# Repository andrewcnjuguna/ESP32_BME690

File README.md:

# ESP32_BME690

Multi-room ESP32-S3 environmental sensor node that streams air-quality data
to a Node.js server over Wi-Fi. Built around the Bosch BME690 with auxiliary
light, sound and battery monitoring.

## Hardware

- ESP32-S3-WROOM-1 module
- Bosch **BME690** (I2C) — temperature, humidity, pressure, IAQ, CO2eq, bVOC
- SH1106 0.96" OLED (I2C)
- TEMT6000 ambient light sensor
- Analog MEMS microphone (sound level)
- 1-cell LiPo with 1M/1M voltage divider on the battery rail
- USB-C power / programming
- Status LED

KiCad project lives in [hardware/kicad/](hardware/kicad/).

### Pin map

| Function    | GPIO |
|-------------|------|
| I2C SDA     | 8    |
| I2C SCL     | 9    |
| Status LED  | 2    |
| Light sensor (TEMT6000) | 5 |
| Microphone  | 4    |
| VBAT sense  | 1    |

## Firmware

Sketches live in [firmware/](firmware/).

- `ESP32_BME690_usb/` — main node firmware
- `battery_level/`, `light_sensor_test/`, `sound_sensor/` — bring-up sketches

### Setup

1. Open `firmware/ESP32_BME690_usb/` in the Arduino IDE.
2. Copy `secrets.h.example` → `secrets.h` and fill in your Wi-Fi credentials
   and server URL. `secrets.h` is gitignored.
3. Install required libraries: `Adafruit GFX`, `Adafruit SH110X`,
   `BSEC2` (Bosch), `ArduinoJson`, `ArduinoOTA`.
4. Build & flash. The `locationID` constant in the sketch tags this node's
   data on the server (e.g. `Kitchen`, `Living_Room`).

### Node web page (port 80)

Each node runs its own tiny status page at `http://<node-ip>/`
(auto-refreshes every 5 s). It shows the live BSEC readings, light / sound /
battery, **WiFi signal** (RSSI in dBm, an approximate 0–100 % quality, and a
label Excellent/Good/Fair/Weak/Poor), and the SD-log status. If the SD card
is mounted it also links `http://<node-ip>/datalog.csv` to download the full
log.

The node's IP is printed on the serial console at boot
(`[INFO] Web UI at http://...`).

WiFi is self-healing: if the router is down at boot (or the link drops
later), the node keeps logging to SD and retries the connection every 30 s
in the background; OTA and the web page start automatically as soon as the
first connection succeeds — no reboot needed.

### Data upload

Every 3 s BSEC cycle the node POSTs a JSON snapshot to `SERVER_URL`
(`/sensor-data` on the dashboard server). The payload includes `location`,
all sensor channels, and the WiFi link quality (`rssi` in dBm plus a derived
`wifiPercent`). Nodes running older firmware simply omit the WiFi fields —
the dashboard shows "not reported (update firmware)" for them.

## Server (dashboard)

A small Node/Express app in [server/](server/) collects POSTs from each node
and serves a per-room dashboard.

```bash
cd server
npm install express
node server.js
```

Then point a browser at `http://<host>:3000`.

- `POST /sensor-data` — nodes push their JSON snapshot here.
- `GET /data` — latest snapshot of every room, as JSON.
- `GET /` — dashboard. Room boxes are created dynamically from whatever
  `location` tags have reported, so adding a node needs **no server change**.
  Each box shows the air-quality channels plus battery and WiFi signal
  quality for that node.

The `pi_server` notes file documents the systemd / iptables setup used on
the home Raspberry Pi.

## Data logging & plotting

### SD card log

The node averages its 3 s BSEC samples and appends **one CSV row per minute**
to `/datalog.csv` on the SD card:

```
boot_id,uptime_s,epoch,synced,temp_c,hum_pct,press_hpa,iaq,iaq_acc,
co2_ppm,voc_ppm,lux,sound_db,sound_avg,sound_peak,batt_v,batt_pct
```

- `boot_id` — power-session counter (persisted in EEPROM), groups rows from
  one uninterrupted run.
- `uptime_s` — seconds since boot (monotonic, rollover-safe).
- `epoch` / `synced` — Unix time and whether NTP had synced when the row was
  written. Rows logged *before* the sync have `epoch=0`, but their true time
  is still recoverable (see below).
- `iaq_acc` — BSEC accuracy 0–3; air-quality values below your chosen
  threshold are warm-up noise.

Grab the file over WiFi from `http://<node-ip>/datalog.csv`, or pull the
card.

### Plotting with `analysis/plot_datalog.py`

```bash
pip install pandas matplotlib
python analysis/plot_datalog.py datalog.csv            # plot a local file
python analysis/plot_datalog.py --ip 192.168.0.65      # fetch straight from the node
python analysis/plot_datalog.py datalog.csv -o out.png # save instead of showing
python analysis/plot_datalog.py datalog.csv --last 48  # last 48 h only
python analysis/plot_datalog.py datalog.csv --min-accuracy 3  # strict AQ filter
```

The script produces six stacked, time-aligned panels: temp+humidity,
pressure, IAQ, CO₂eq+VOCeq, light+sound, and battery. Under the hood it:

1. **Reconstructs absolute time.** For each `boot_id` it derives
   `boot_epoch = epoch − uptime_s` from the NTP-synced rows, then stamps
   *every* row of that session as `boot_epoch + uptime_s` — so even rows
   logged before the NTP sync get correct timestamps. Sessions that never
   synced have no time anchor and are dropped with a warning.
2. **Masks warm-up air-quality data.** IAQ/CO₂/VOC are blanked where
   `iaq_acc < --min-accuracy` (default 1) so BSEC's calibration period
   doesn't draw misleading flat lines.
3. **Breaks lines at gaps.** Rows are minutely, so a jump larger than
   `--gap-min` (default 5 min) means the node was off; a NaN break is
   inserted so downtime shows as a blank gap instead of a false straight
   line across it.

## Repo layout

```
firmware/   Arduino sketches (main + bring-up)
server/     Node/Express dashboard
analysis/   plot_datalog.py — CSV log plotting
hardware/   KiCad project + design notes
images/     PCB photos
```

Component datasheets are kept locally only (not redistributable).

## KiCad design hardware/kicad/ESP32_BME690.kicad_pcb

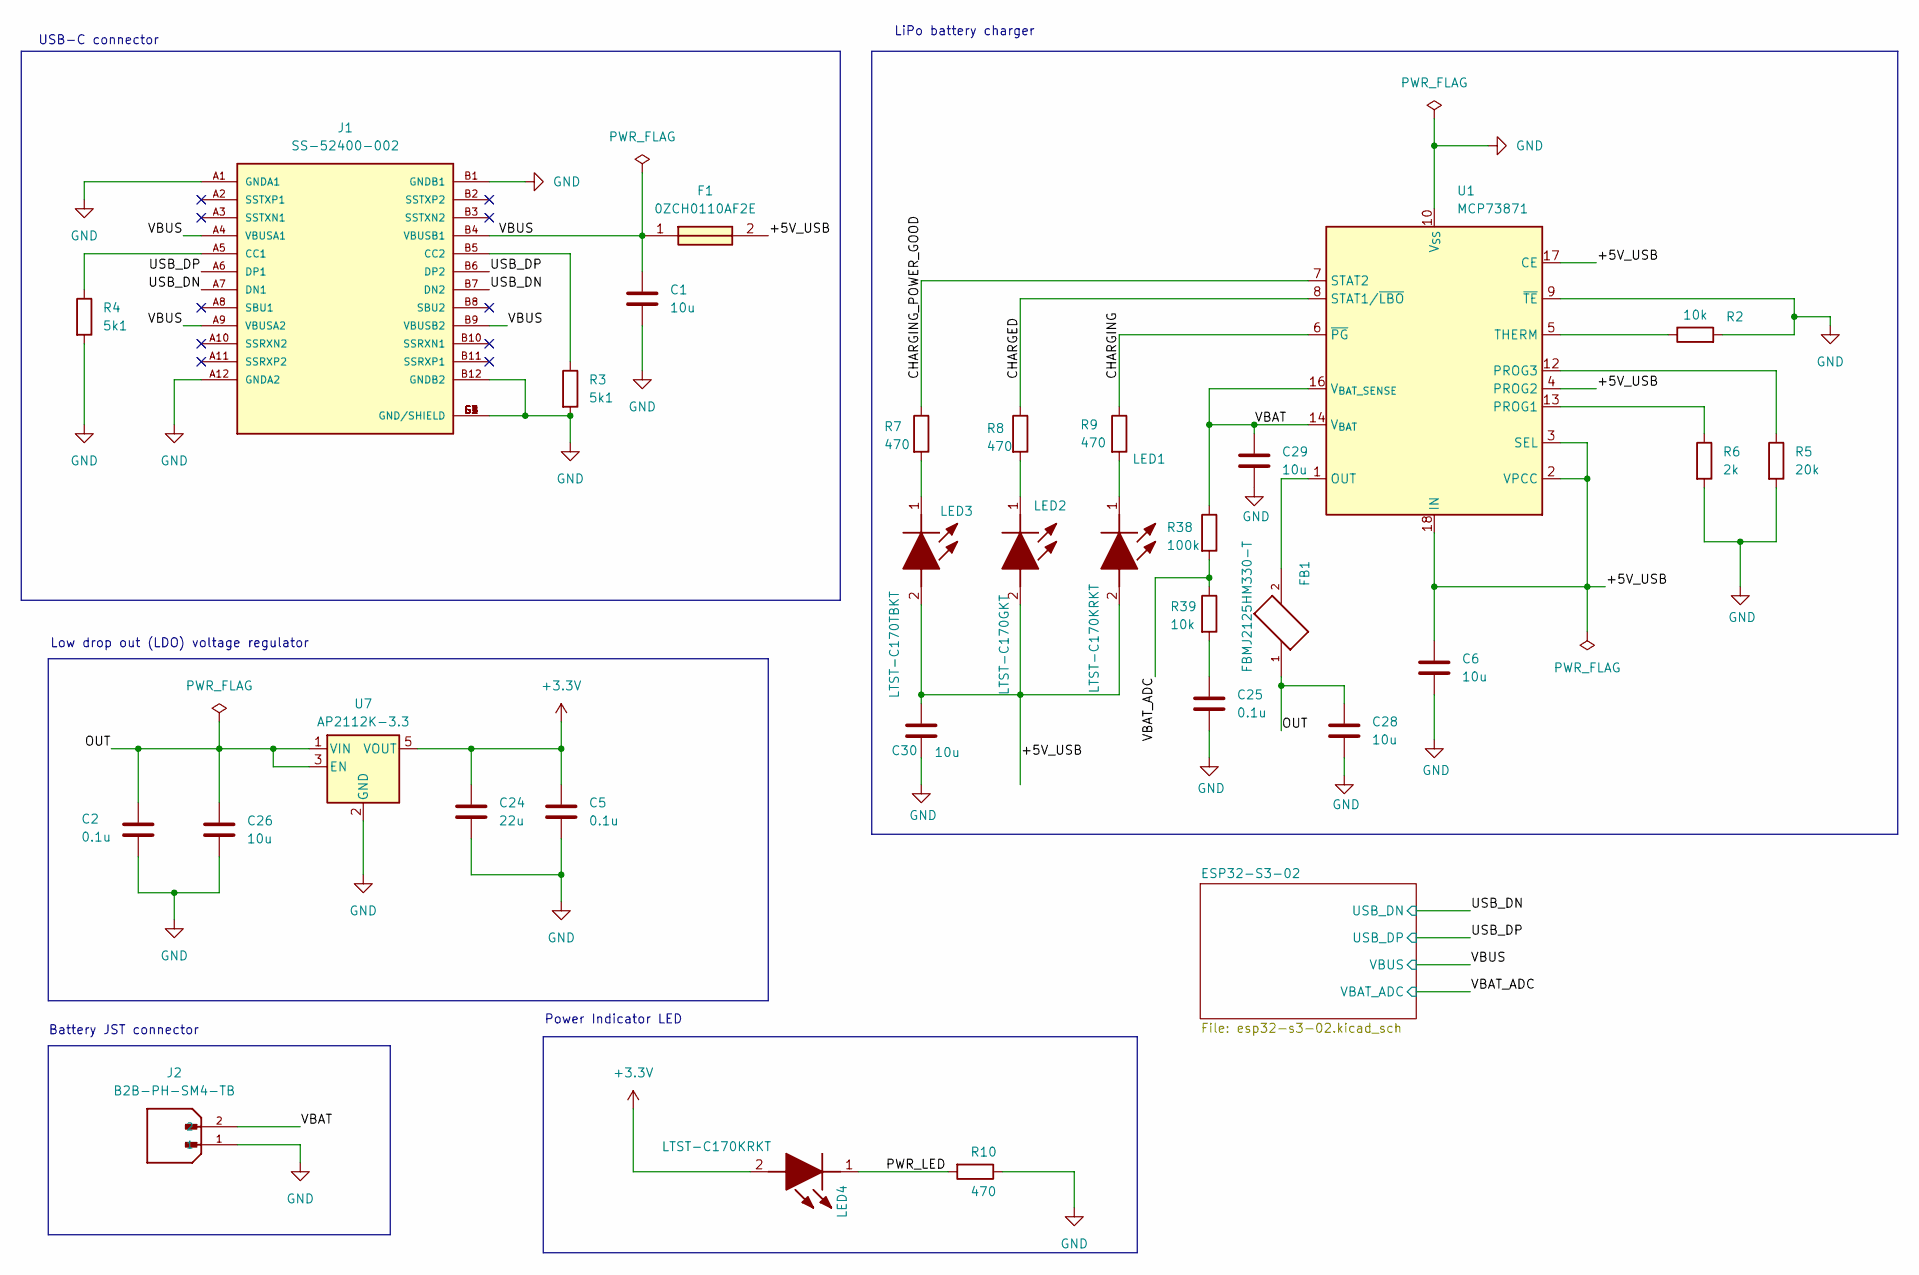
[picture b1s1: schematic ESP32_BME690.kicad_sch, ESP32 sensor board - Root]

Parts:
C1, C6, C26, C28, C29, C30: 10u; C_0805_2012Metric
C2, C5, C25: 0.1u; C_0805_2012Metric
C24: 22u; C_0805_2012Metric
F1: 0ZCH0110AF2E; FUSC3226X100N; Manufacturer_Part_Number 0ZCH0110AF2E
FB1: FBMJ2125HM330-T; BEADC2012X105N
J1: SS-52400-002; BELFUSE_SS-52400-002; PARTREV A0
J2: B2B-PH-SM4-TB; JST_B2B-PH-SM4-TB; PARTREV N/A
LED1, LED4: LTST-C170KRKT; LEDC2012X120N; Manufacturer_Part_Number LTST-C170KRKT; Mouser Part Number 859-LTST-C170KRKT
LED2: LTST-C170GKT; LEDC2012X120N; Manufacturer_Part_Number LTST-C170GKT; Mouser Part Number 859-LTST-C170GKT
LED3: LTST-C170TBKT; LEDC2012X120N; Manufacturer_Part_Number LTST-C170TBKT; Mouser Part Number 859-LTST-C170TBKT
R2, R39: 10k; R_0805_2012Metric
R3, R4: 5k1; R_0805_2012Metric
R5: 20k; R_0805_2012Metric
R6: 2k; R_0805_2012Metric
R7, R8, R9, R10: 470; R_0805_2012Metric
R38: 100k; R_0805_2012Metric
U1: MCP73871; QFN-20-1EP_4x4mm_P0.5mm_EP2.5x2.5mm
U7: AP2112K-3.3; SOT-23-5

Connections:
+3.3V: C5.1, C24.1, LED4.2 (A), U7.5 (VOUT); also elsewhere on the board
/+5V_USB: C6.1, C30.1, F1.2, LED1.2 (A), LED2.2 (A), LED3.2 (A), U1.2 (VPCC), U1.3 (SEL), U1.4 (PROG2), U1.17 (CE), U1.18 (IN), U1.19 (IN)
/CHARGED: R8.1, U1.8 (STAT1/~LBO)
/CHARGING: R9.1, U1.6 (~PG)
/CHARGING_POWER_GOOD: R7.1, U1.7 (STAT2)
/OUT: C2.1, C26.1, C28.1, FB1.1, U7.1 (VIN), U7.3 (EN)
/PWR_LED: LED4.1 (K), R10.2
/USB_DN: J1.A7 (DN1), J1.B7 (DN2); also elsewhere on the board
/USB_DP: J1.A6 (DP1), J1.B6 (DP2); also elsewhere on the board
/VBAT: C29.1, J2.2, R38.1, U1.14 (V_{BAT}), U1.15 (V_{BAT}), U1.16 (V_{BAT_SENSE})
/VBAT_ADC: R38.2, R39.1; also elsewhere on the board
/VBUS: C1.1, F1.1, J1.A4 (VBUSA1), J1.A9 (VBUSA2), J1.B4 (VBUSB1), J1.B9 (VBUSB2); also elsewhere on the board
GND: C1.2, C2.2, C5.2, C6.2, C24.2, C25.2, C26.2, C28.2, C29.2, C30.2, J1.A1 (GNDA1), J1.A12 (GNDA2), J1.B1 (GNDB1), J1.B12 (GNDB2), J1.G1 (GND/SHIELD), J1.G2 (GND/SHIELD), J1.G3 (GND/SHIELD), J1.G4 (GND/SHIELD), J1.S1 (GND/SHIELD), J1.S2 (GND/SHIELD), J1.S3 (GND/SHIELD), J1.S4 (GND/SHIELD), J2.1, R2.2, R3.2, R4.2, R5.2, R6.2, R10.1, U1.9 (~TE), U1.10 (V_{SS}), U1.11 (V_{SS}), U1.21 (V_{SS}), U7.2 (GND); also elsewhere on the board
unnamed: C25.1, R39.2
unnamed: FB1.2, U1.1 (OUT), U1.20 (OUT)
unnamed: J1.A5 (CC1), R4.1
unnamed: J1.B5 (CC2), R3.1
unnamed: LED1.1 (K), R9.2
unnamed: LED2.1 (K), R8.2
unnamed: LED3.1 (K), R7.2
unnamed: R6.1, U1.13 (PROG1)
unnamed: R5.1, U1.12 (PROG3)
unnamed: R2.1, U1.5 (THERM)

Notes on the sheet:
Battery JST connector
LiPo battery charger
Power Indicator LED
USB-C connector
Low drop out (LDO) voltage regulator

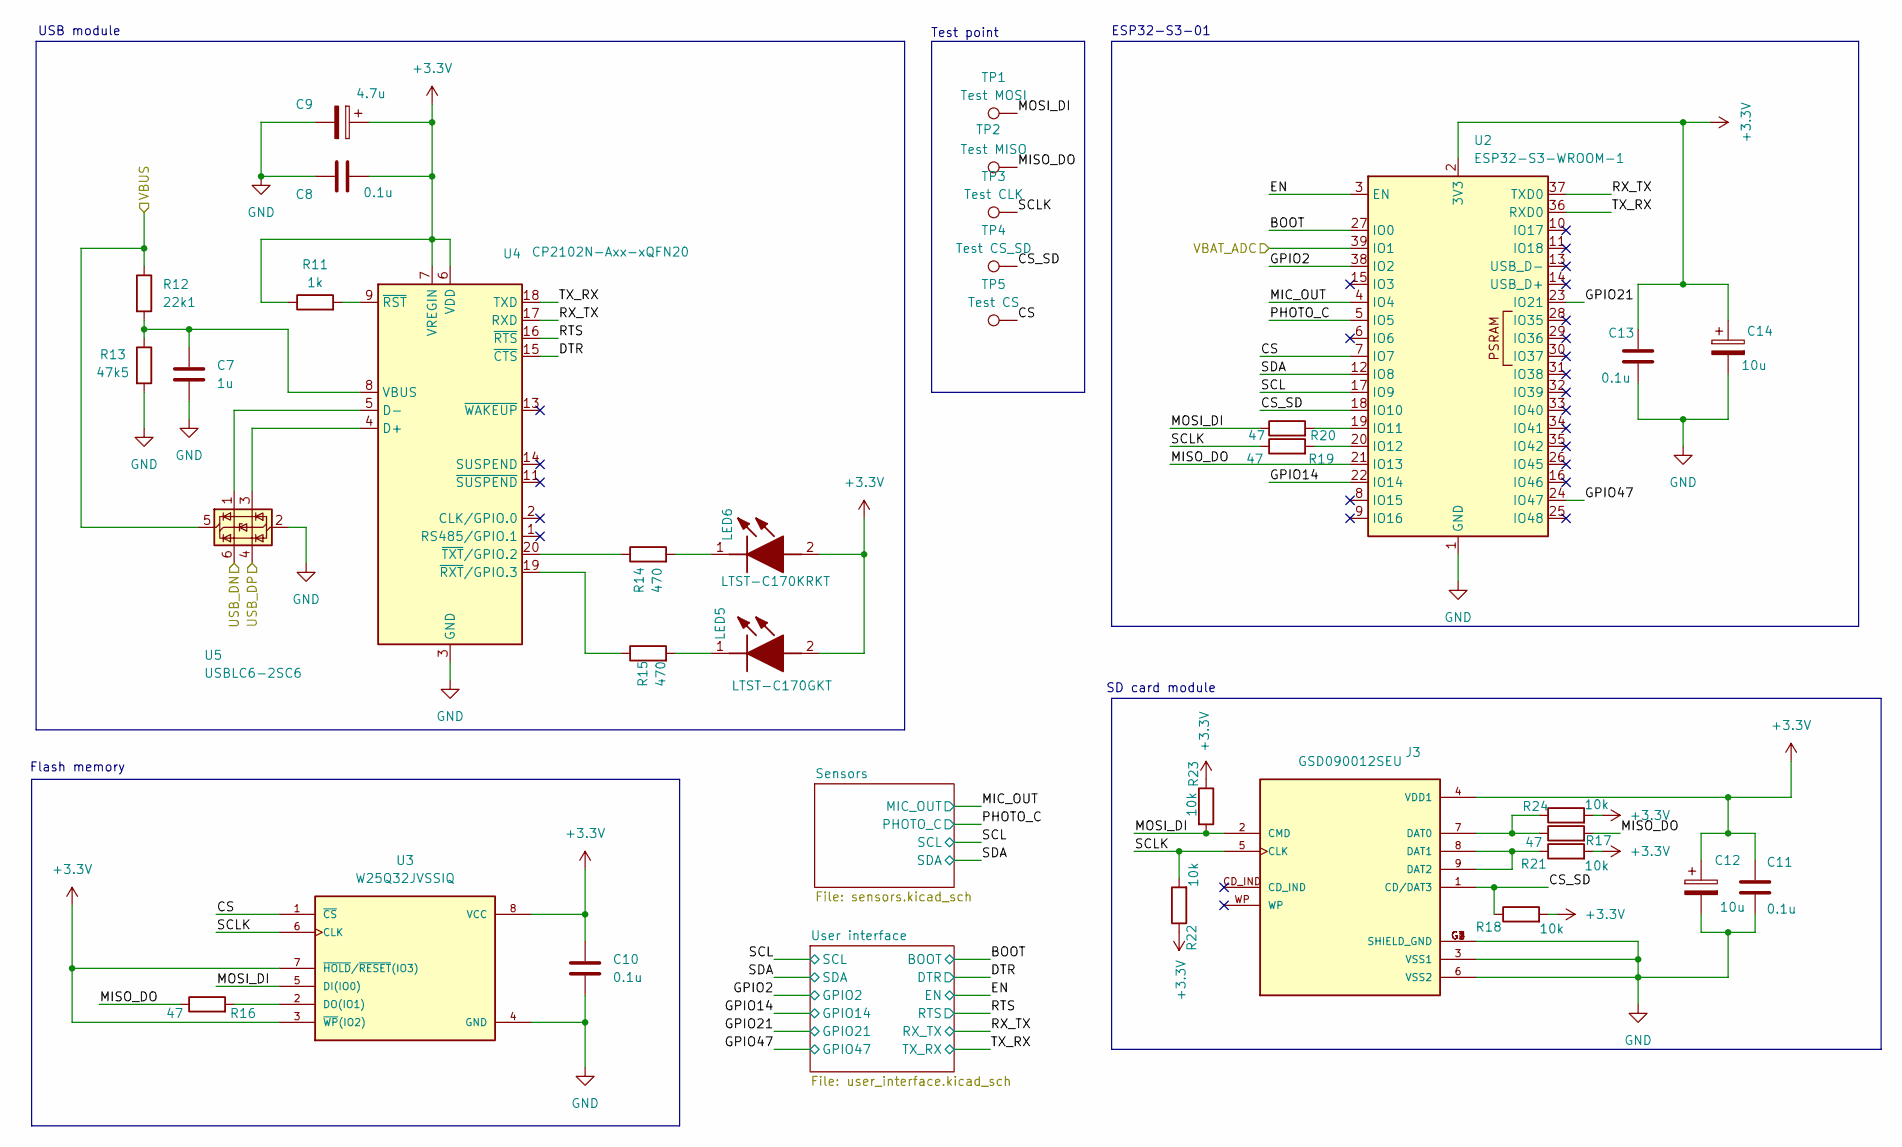
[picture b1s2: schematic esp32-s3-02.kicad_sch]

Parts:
C7: 1u; C_0805_2012Metric
C8, C10, C11, C13: 0.1u; C_0805_2012Metric
C9: 4.7u; T491A
C12, C14: 10u; T491A
J3: GSD090012SEU; AMPHENOL_GSD090012SEU; PARTREV E
LED5: LTST-C170GKT; LEDC2012X120N; Manufacturer_Part_Number LTST-C170GKT; Mouser Part Number 859-LTST-C170GKT
LED6: LTST-C170KRKT; LEDC2012X120N; Manufacturer_Part_Number LTST-C170KRKT; Mouser Part Number 859-LTST-C170KRKT
R11: 1k; R_0805_2012Metric
R12: 22k1; R_0805_2012Metric
R13: 47k5; R_0805_2012Metric
R14, R15: 470; R_0805_2012Metric
R16, R17, R19, R20: 47; R_0805_2012Metric
R18, R21, R22, R23, R24: 10k; R_0805_2012Metric
TP1: Test MOSI; TestPoint_Pad_D1.0mm
TP2: Test MISO; TestPoint_Pad_D1.0mm
TP3: Test CLK; TestPoint_Pad_D1.0mm
TP4: Test CS_SD; TestPoint_Pad_D1.0mm
TP5: Test CS; TestPoint_Pad_D1.0mm
U2: ESP32-S3-WROOM-1
U3: W25Q32JVSSIQ; SOIC127P790X216-8N; M_PART_NUMBER W25QXX
U4: CP2102N-Axx-xQFN20; SiliconLabs_QFN-20-1EP_3x3mm_P0.5mm_EP1.8x1.8mm
U5: USBLC6-2SC6; SOT-23-6

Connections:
+3.3V: C8.2, C9.1, C10.1, C11.1, C12.1, C13.1, C14.1, J3.4 (VDD1), LED5.2 (A), LED6.2 (A), R11.1, R18.2, R21.2, R22.1, R23.1, R24.2, U2.2 (3V3), U3.3 (~WP(IO2)), U3.7 (~HOLD/~RESET(IO3)), U3.8 (VCC), U4.6 (VDD), U4.7 (VREGIN); also elsewhere on the board
/ESP32-S3-02/BOOT: U2.27 (IO0); also elsewhere on the board
/ESP32-S3-02/CS: TP5.1 (1_1), U2.7 (IO7), U3.1 (~CS)
/ESP32-S3-02/CS_SD: J3.1 (CD/DAT3), R18.1, TP4.1 (1_1), U2.18 (IO10)
/ESP32-S3-02/DTR: U4.15 (~CTS); also elsewhere on the board
/ESP32-S3-02/EN: U2.3 (EN); also elsewhere on the board
/ESP32-S3-02/GPIO2: U2.38 (IO2); also elsewhere on the board
/ESP32-S3-02/GPIO14: U2.22 (IO14); also elsewhere on the board
/ESP32-S3-02/GPIO21: U2.23 (IO21); also elsewhere on the board
/ESP32-S3-02/GPIO47: U2.24 (IO47); also elsewhere on the board
/ESP32-S3-02/MIC_OUT: U2.4 (IO4); also elsewhere on the board
/ESP32-S3-02/MISO_DO: R16.1, R17.2, TP2.1 (1_1), U2.21 (IO13)
/ESP32-S3-02/MOSI_DI: J3.2 (CMD), R20.1, R23.2, TP1.1 (1_1), U3.5 (DI(IO0))
/ESP32-S3-02/PHOTO_C: U2.5 (IO5); also elsewhere on the board
/ESP32-S3-02/RTS: U4.16 (~RTS); also elsewhere on the board
/ESP32-S3-02/RX_TX: U2.37 (TXD0), U4.17 (RXD); also elsewhere on the board
/ESP32-S3-02/SCL: U2.17 (IO9); also elsewhere on the board
/ESP32-S3-02/SCLK: J3.5 (CLK), R19.1, R22.2, TP3.1 (1_1), U3.6 (CLK)
/ESP32-S3-02/SDA: U2.12 (IO8); also elsewhere on the board
/ESP32-S3-02/TX_RX: U2.36 (RXD0), U4.18 (TXD); also elsewhere on the board
/USB_DN: U5.6 (I/O1); also elsewhere on the board
/USB_DP: U5.4 (I/O2); also elsewhere on the board
/VBAT_ADC: U2.39 (IO1); also elsewhere on the board
/VBUS: R12.1, U5.5 (VBUS); also elsewhere on the board
GND: C7.2, C8.1, C9.2, C10.2, C11.2, C12.2, C13.2, C14.2, J3.3 (VSS1), J3.6 (VSS2), J3.G1 (SHIELD_GND), J3.G2 (SHIELD_GND), J3.G3 (SHIELD_GND), J3.G4 (SHIELD_GND), R13.2, U2.1 (GND), U2.40 (GND), U2.41 (GND), U3.4 (GND), U4.3 (GND), U4.12 (GND), U4.21 (GND), U5.2 (GND); also elsewhere on the board
unnamed: J3.7 (DAT0), R17.1, R24.1
unnamed: J3.8 (DAT1), J3.9 (DAT2), R21.1
unnamed: LED5.1 (K), R15.2
unnamed: LED6.1 (K), R14.2
unnamed: R20.2, U2.19 (IO11)
unnamed: R19.2, U2.20 (IO12)
unnamed: R16.2, U3.2 (DO(IO1))
unnamed: U4.4 (D+), U5.3 (I/O2)
unnamed: U4.5 (D-), U5.1 (I/O1)
unnamed: C7.1, R12.2, R13.1, U4.8 (VBUS)
unnamed: R11.2, U4.9 (~RST)
unnamed: R15.1, U4.19 (~RXT/GPIO.3)
unnamed: R14.1, U4.20 (~TXT/GPIO.2)

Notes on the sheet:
ESP32-S3-01
Flash memory
SD card module
USB module
Test point

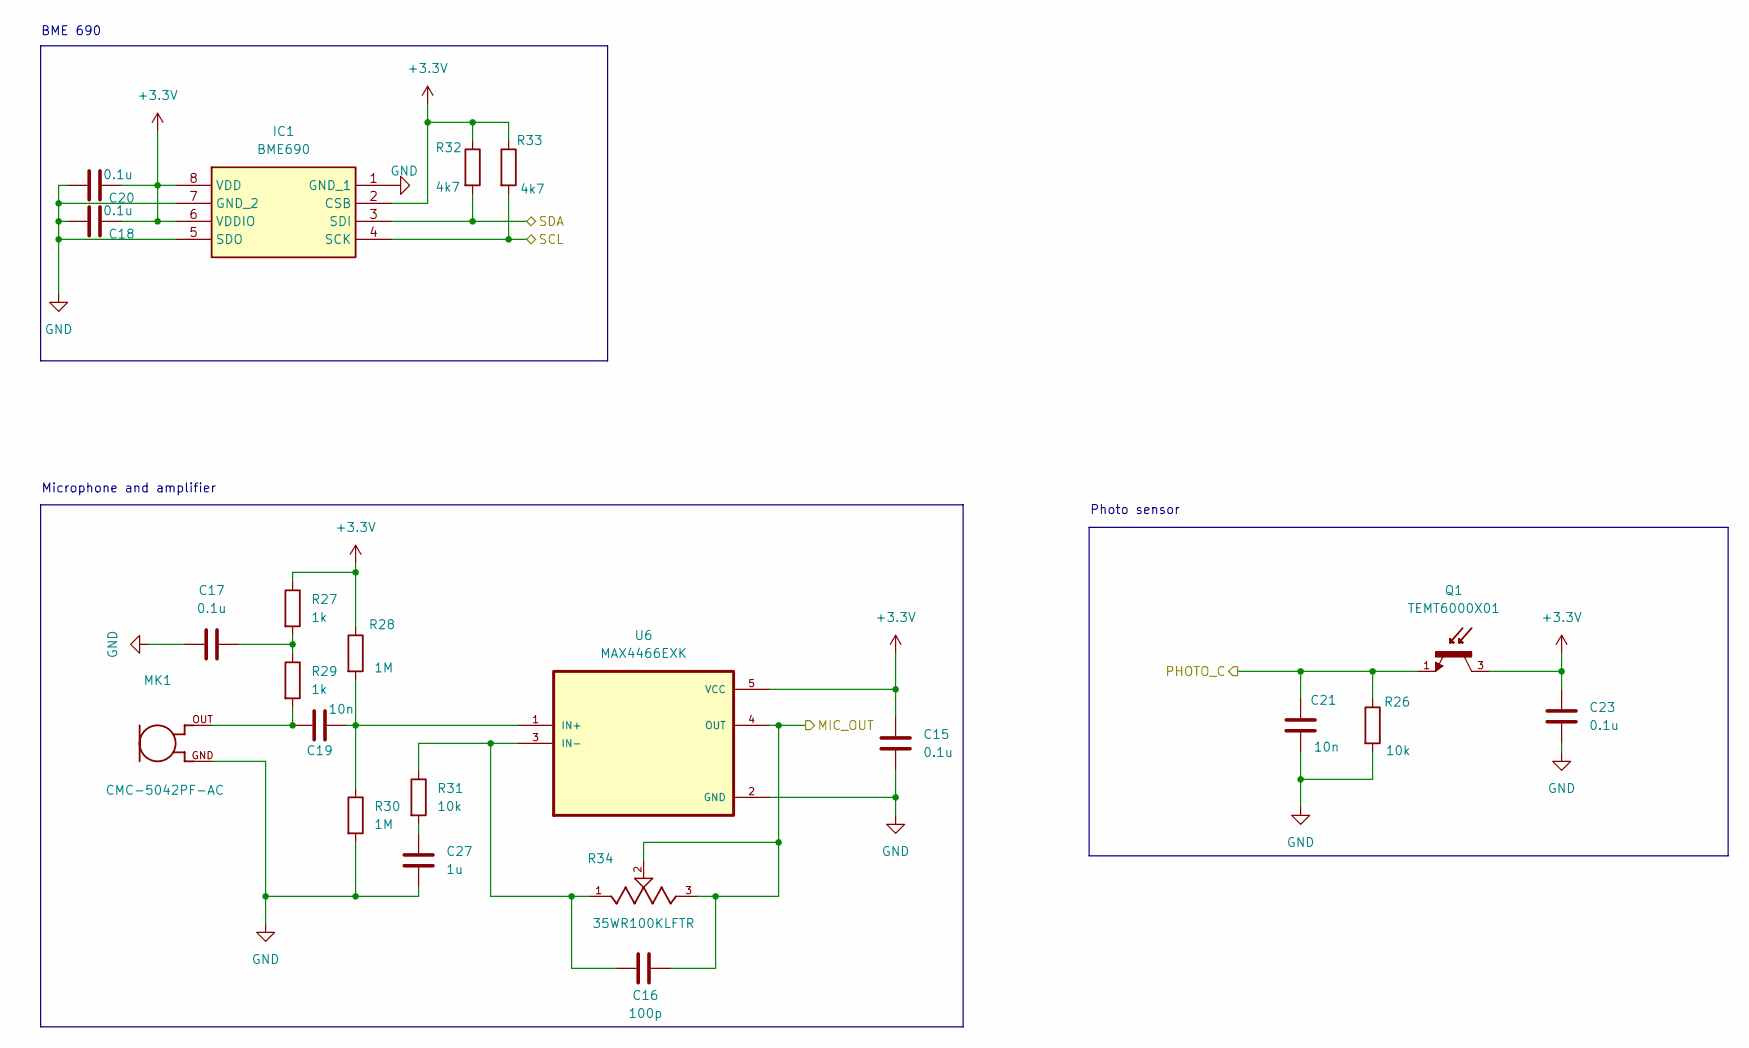
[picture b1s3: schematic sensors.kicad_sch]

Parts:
C15, C17, C18, C20, C23: 0.1u; C_0805_2012Metric
C16: 100p; C_0805_2012Metric
C19, C21: 10n; C_0805_2012Metric
C27: 1u; C_0805_2012Metric
IC1: BME690; Manufacturer_Part_Number BME690; Mouser Part Number 262-BME690
MK1: CMC-5042PF-AC; CUI_CMC-5042PF-AC
Q1: TEMT6000X01; TRANS_TEMT6000X01; PARTREV 1.9
R26, R31: 10k; R_0805_2012Metric
R27, R29: 1k; R_0805_2012Metric
R28, R30: 1M; R_0805_2012Metric
R32, R33: 4k7; R_0805_2012Metric
R34: 35WR100KLFTR; TRIM_35WR100KLFTR; PARTREV D
U6: MAX4466EXK; SOT65P210X110-5N

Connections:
+3.3V: C15.1, C18.1, C20.1, C23.1, IC1.2 (CSB), IC1.6 (VDDIO), IC1.8 (VDD), Q1.3, R27.1, R28.1, R32.1, R33.1, U6.5 (VCC); also elsewhere on the board
/ESP32-S3-02/MIC_OUT: C16.2, R34.2, R34.3, U6.4 (OUT); also elsewhere on the board
/ESP32-S3-02/PHOTO_C: C21.1, Q1.1, R26.1; also elsewhere on the board
/ESP32-S3-02/SCL: IC1.4 (SCK), R33.2; also elsewhere on the board
/ESP32-S3-02/SDA: IC1.3 (SDI), R32.2; also elsewhere on the board
GND: C15.2, C17.1, C18.2, C20.2, C21.2, C23.2, C27.1, IC1.1 (GND_1), IC1.5 (SDO), IC1.7 (GND_2), MK1.GND, R26.2, R30.2, U6.2 (GND); also elsewhere on the board
unnamed: C17.2, R27.2, R29.1
unnamed: C19.1, MK1.OUT, R29.2
unnamed: C27.2, R31.2
unnamed: C19.2, R28.2, R30.1, U6.1 (IN+)
unnamed: C16.1, R31.1, R34.1, U6.3 (IN-)

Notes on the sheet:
BME 690
Microphone and amplifier
Photo sensor

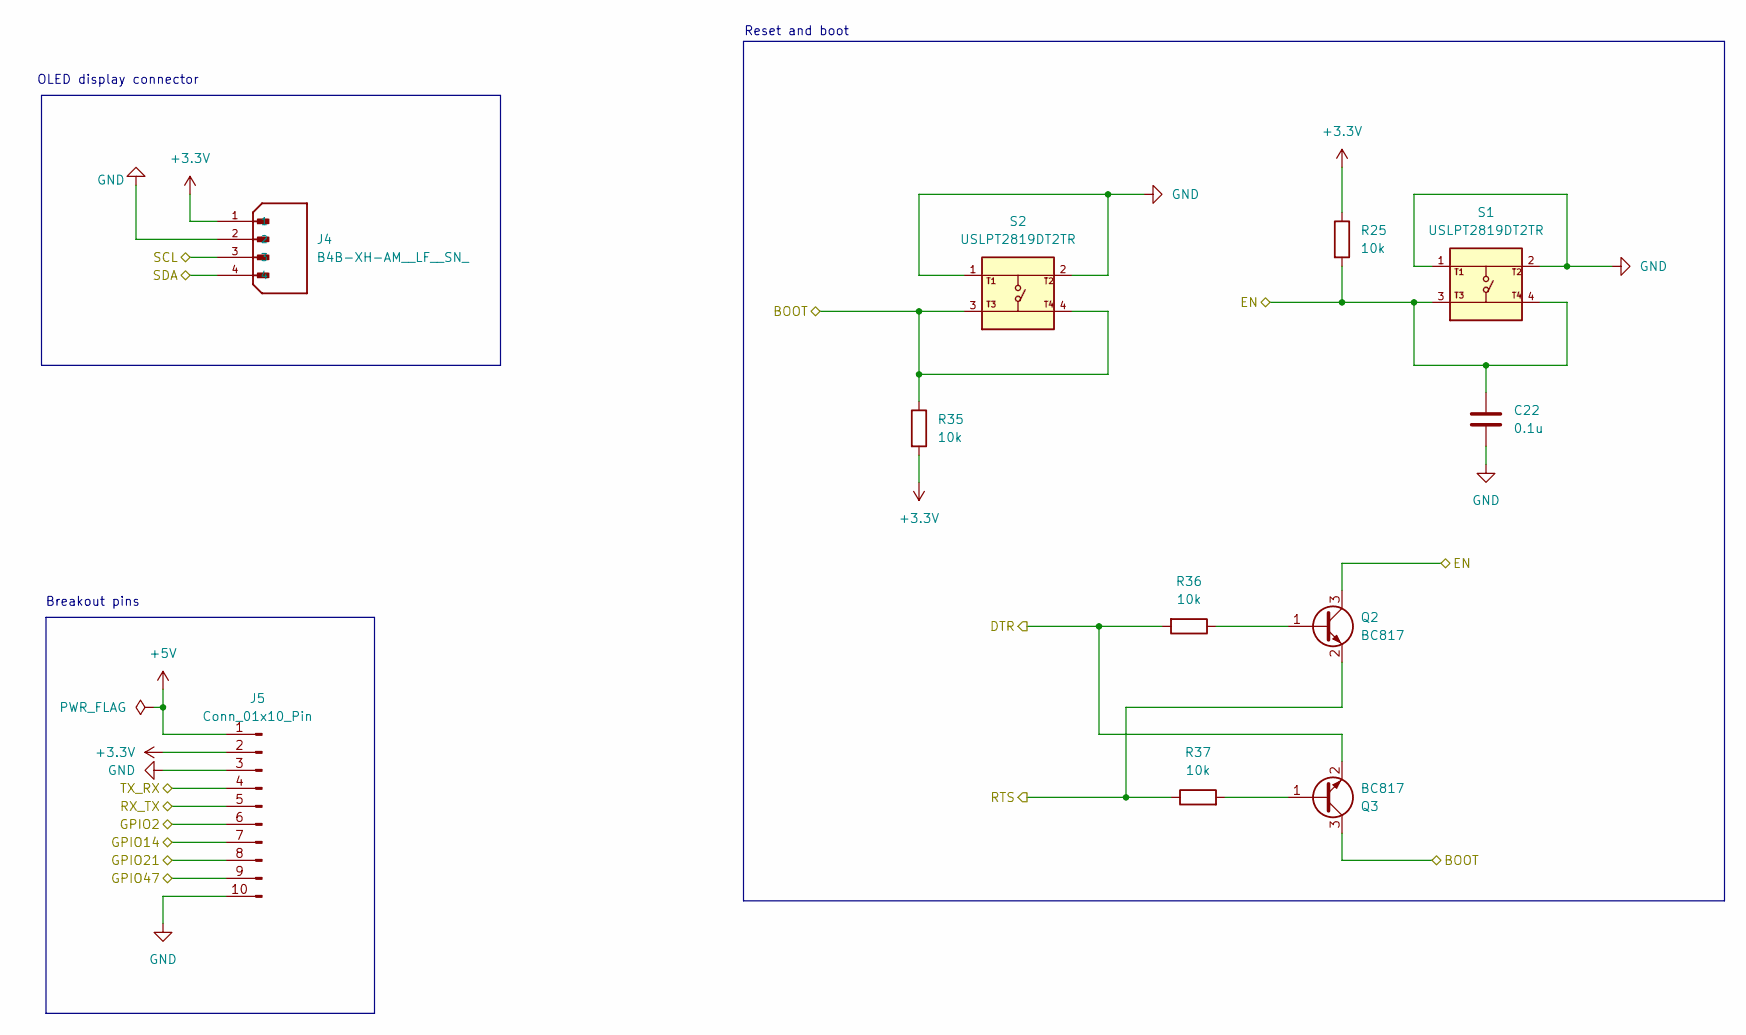
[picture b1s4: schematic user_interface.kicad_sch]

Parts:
C22: 0.1u; C_0805_2012Metric
J4: B4B-XH-AM__LF__SN_; JST_B4B-XH-AM__LF__SN_; PARTREV N/A
J5: Conn_01x10_Pin; PinHeader_1x10_P2.54mm_Vertical
Q2, Q3: BC817; SOT-23
R25, R35, R36, R37: 10k; R_0805_2012Metric
S1, S2: USLPT2819DT2TR; SW_USLPT2819DT2TR; PARTREV P

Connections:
+3.3V: J4.1, J5.2, R25.1, R35.2; also elsewhere on the board
+5V: J5.1
/ESP32-S3-02/BOOT: Q3.3 (C), R35.1, S2.3, S2.4; also elsewhere on the board
/ESP32-S3-02/DTR: Q3.2 (E), R36.2; also elsewhere on the board
/ESP32-S3-02/EN: C22.1, Q2.3 (C), R25.2, S1.3, S1.4; also elsewhere on the board
/ESP32-S3-02/GPIO2: J5.6; also elsewhere on the board
/ESP32-S3-02/GPIO14: J5.7; also elsewhere on the board
/ESP32-S3-02/GPIO21: J5.8; also elsewhere on the board
/ESP32-S3-02/GPIO47: J5.9; also elsewhere on the board
/ESP32-S3-02/RTS: Q2.2 (E), R37.1; also elsewhere on the board
/ESP32-S3-02/RX_TX: J5.5; also elsewhere on the board
/ESP32-S3-02/SCL: J4.3; also elsewhere on the board
/ESP32-S3-02/SDA: J4.4; also elsewhere on the board
/ESP32-S3-02/TX_RX: J5.4; also elsewhere on the board
GND: C22.2, J4.2, J5.3, J5.10, S1.1, S1.2, S2.1, S2.2; also elsewhere on the board
unnamed: Q2.1 (B), R36.1
unnamed: Q3.1 (B), R37.2

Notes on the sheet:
Reset and boot
Breakout pins
OLED display connector

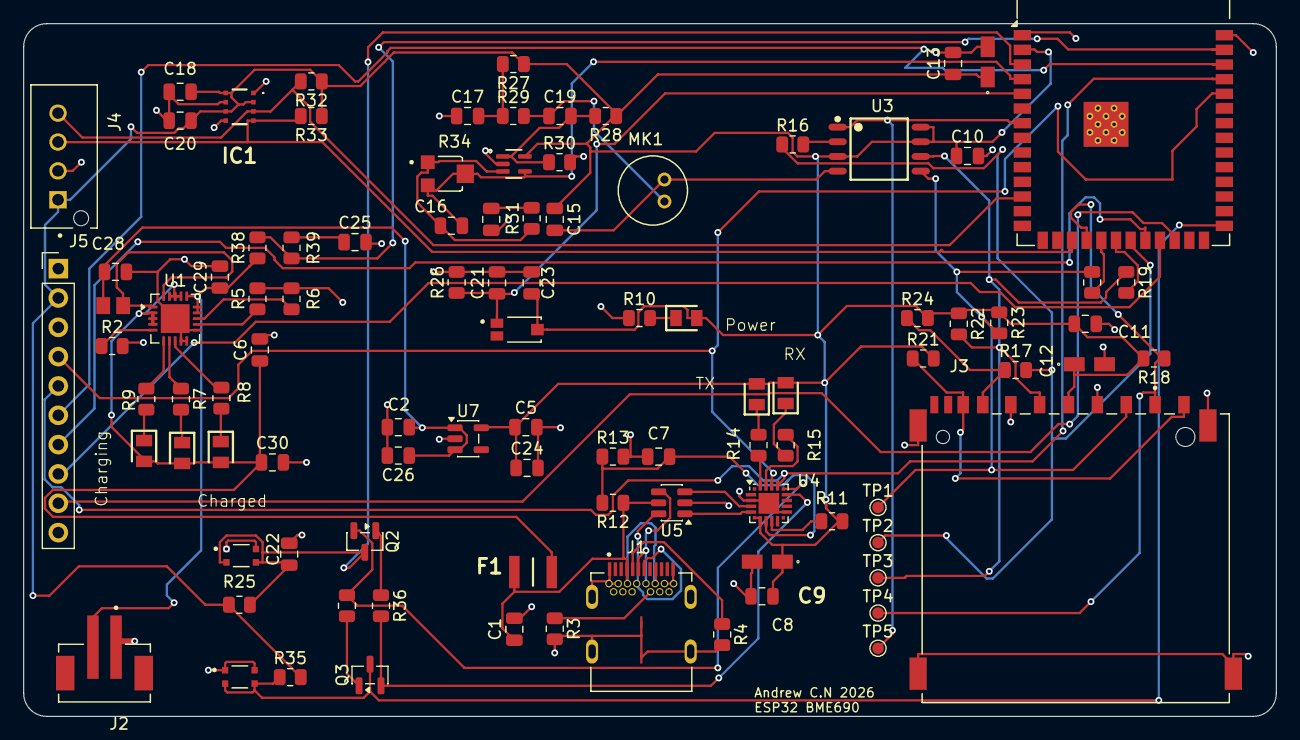
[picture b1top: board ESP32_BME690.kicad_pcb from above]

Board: 4 copper layers, 108.5 x 60.0 mm, 98 parts (0 on the bottom side), 62 nets.

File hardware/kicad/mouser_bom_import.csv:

Manufacturer Part Number,Quantity
BME690,1
0ZCH0110AF2E,1
FBMJ2125HM330-T,1
SS-52400-002,1
B2B-PH-SM4-TB,1
GSD090012SEU,1
B4B-XH-AM(LF)(SN),1
CMC-5042PF-AC,1
TEMT6000X01,1
BC817,2
35WR100KLFTR,1
USLPT2819DT2TR,2
MCP73871,1
ESP32-S3-WROOM-1,1
W25Q32JVSSIQ,1
CP2102N-A01-GQFN20,1
USBLC6-2SC6,1
MAX4466EXK,1
AP2112K-3.3,1
T491A106K016AT,2
T491A475K016AT,1

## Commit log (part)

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2026-05-05 Initial commit: ESP32-S3 BME690 sensor node + dashboard
2026-05-06 some changes to improve sound sensor values
2026-05-10 small changes to the kicad script
